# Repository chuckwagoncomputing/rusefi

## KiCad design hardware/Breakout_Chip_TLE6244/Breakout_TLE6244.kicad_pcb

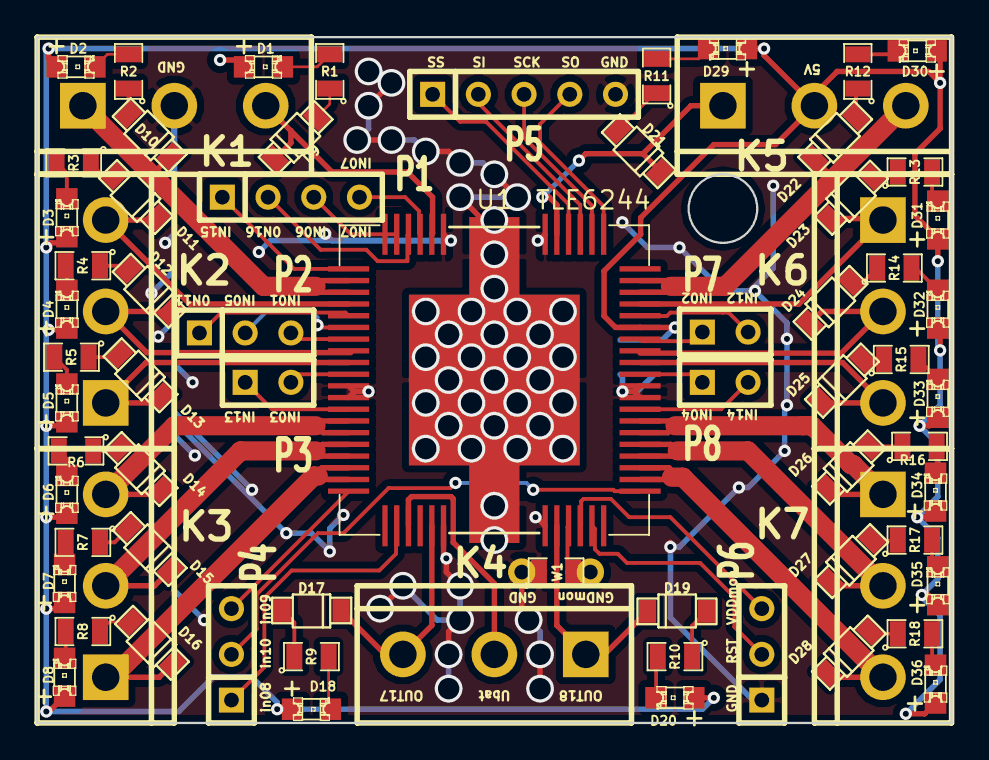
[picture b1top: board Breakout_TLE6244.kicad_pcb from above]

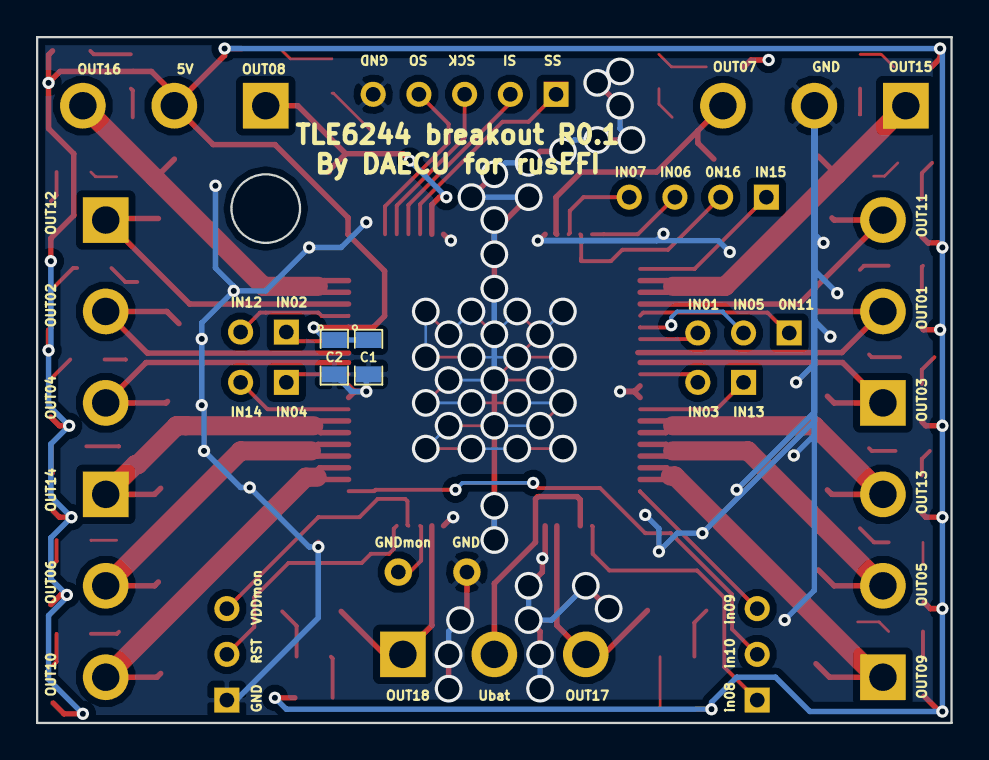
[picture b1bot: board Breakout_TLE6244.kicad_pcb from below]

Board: 4 copper layers, 50.8 x 38.1 mm, 73 parts (2 on the bottom side), 80 nets.

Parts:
C1: 1uF; SM0805
C2: .01uF; SM0805
D1, D2, D3, D4, D5, D6, D7, D8, D18, D20, D29, D30, D31, D32, D33, D34, D35, D36: LED-red; LED-0805_A
D9, D10, D11, D12, D13, D14, D15, D16, D17, D19, D21, D22, D23, D24, D25, D26, D27, D28: DIODE; SOD-123
K1, K2, K3, K4, K5, K6, K7: CONN_3; bornier3
P1: CONN_4; SIL-4
P2, P4, P6: CONN_3; SIL-3
P3, P7, P8: CONN_2; SIL-2
P5: CONN_5; SIL-5
R1, R2, R3, R4, R5, R6, R7, R8, R9, R10, R11, R12, R13, R14, R15, R16, R17, R18: 1K; SM0805
U1: TLE6244; HiQUAD64
W1: TEST; SM0805_jumper

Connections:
/5v: C1.1, C2.1, D1.1, D2.1, D3.1, D4.1, D5.1, D6.1, D7.1, D8.1, D18.1, D20.1, D29.1, D30.1, D31.1, D32.1, D33.1, D34.1, D35.1, D36.1, K5.2, U1.47
/GNDmon: U1.29, W1.2
/RST: P6.2, U1.31
/SCK: P5.3, U1.54
/SI: P5.2, U1.55
/SO: P5.4, U1.53
/SS: P5.1, U1.56
/Ubatt: K4.2, U1.23
/VDDmon: P6.3, U1.30
/in01: P2.3, U1.7
/in02: P7.1, U1.46
/in03: P3.2, U1.10
/in04: P8.1, U1.43
/in05: P2.2, U1.6
/in06: P1.3, U1.63, U1.64
/in07: P1.4, U1.61
/in08: P4.1, U1.22
/in09: P4.3, U1.20
/in10: P4.2, U1.33
/in11: P2.1, U1.5
/in12: P7.2, U1.48
/in13: P3.1, U1.13
/in14: P8.2, U1.40
/in15: P1.1, U1.1
/in16: P1.2, U1.62
/out01: D12.2, K2.2, U1.8
/out02: D24.2, K6.2, U1.45
/out03: D13.2, K2.1, U1.9
/out04: D25.2, K6.3, U1.44
/out05: D15.2, K3.2, U1.16, U1.17
/out06: D27.2, K7.2, U1.36, U1.37
/out07: D9.2, K1.3, U1.60
/out08: D21.2, K5.1, U1.57
/out09: D16.2, K3.1, U1.18, U1.19
/out10: D28.2, K7.3, U1.34, U1.35
/out11: D11.2, K2.3, U1.4
/out12: D23.2, K6.1, U1.49
/out13: D14.2, K3.3, U1.14, U1.15
/out14: D26.2, K7.1, U1.38, U1.39
/out15: D10.2, K1.1, U1.2, U1.3
/out16: D22.2, K5.3, U1.50, U1.51
/out17: D17.2, K4.3, U1.25
/out18: D19.2, K4.1, U1.28
GND: C1.2, C2.2, K1.2, P5.5, P6.1, U1.11, U1.12, U1.26, U1.27, U1.41, U1.42, U1.58, U1.59, U1.slug, W1.1
unnamed: D9.1, R1.1
unnamed: D21.1, R11.1
unnamed: D29.2, R11.2
unnamed: D1.2, R1.2
unnamed: D17.1, R9.1
unnamed: D18.2, R9.2
unnamed: D3.2, R3.2
unnamed: D11.1, R3.1
unnamed: D22.1, R12.1
unnamed: D30.2, R12.2
unnamed: D2.2, R2.2
unnamed: D10.1, R2.1
unnamed: D27.1, R17.1
unnamed: D28.1, R18.1
unnamed: D36.2, R18.2
unnamed: D35.2, R17.2
unnamed: D26.1, R16.1
unnamed: D34.2, R16.2
unnamed: D25.1, R15.1
unnamed: D33.2, R15.2
unnamed: D19.1, R10.1
unnamed: D20.2, R10.2
unnamed: D5.2, R5.2
unnamed: D7.2, R7.2
unnamed: D15.1, R7.1
unnamed: D14.1, R6.1
unnamed: D6.2, R6.2
unnamed: D13.1, R5.1
unnamed: D12.1, R4.1
unnamed: D4.2, R4.2
unnamed: D24.1, R14.1
unnamed: D32.2, R14.2
unnamed: D23.1, R13.1
unnamed: D31.2, R13.2
unnamed: D16.1, R8.1
unnamed: D8.2, R8.2

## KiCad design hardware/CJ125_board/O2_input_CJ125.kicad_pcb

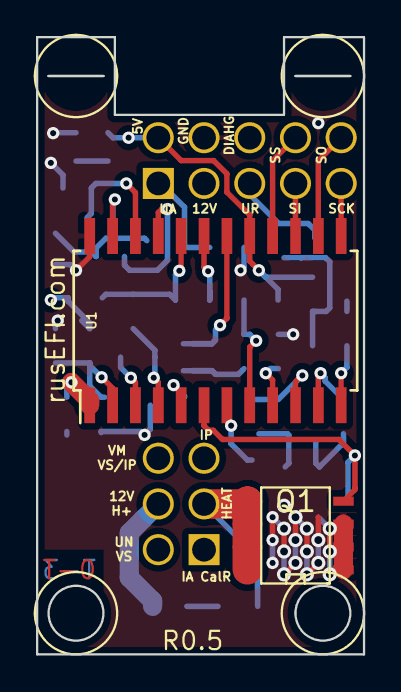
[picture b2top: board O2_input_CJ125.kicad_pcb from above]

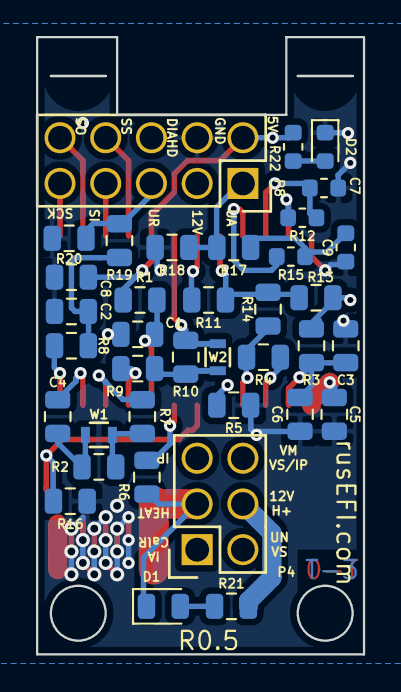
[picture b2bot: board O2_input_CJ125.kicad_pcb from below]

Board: 4 copper layers, 18.2 x 34.3 mm, 39 parts (37 on the bottom side), 35 nets.

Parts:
C1: 1000pF; C_0805_2012Metric
C2, C6, C8: 0.033uF; C_0805_2012Metric
C3: DNP; C_0805_2012Metric
C4: 0.1uF; C_0805_2012Metric
C5: 220pf; C_0805_2012Metric
C7: 0.1uF; C_0603_1608Metric
C9: 0.033uF; C_0603_1608Metric
D1: LED-RED; LED_0805_2012Metric
D2: LED-GRN; LED_0603_1608Metric
P4: CONN_02X03; Socket_Strip_Straight_2x03
P8: CONN_02X05; Socket_Strip_Straight_2x05
Q1: FDS2734; SO8E_ST
R1, R5, R7, R16, R18, R20: 10k; R_0805_2012Metric
R2: 21k6; R_0805_2012Metric
R3: 0R; R_0805_2012Metric
R4: 61.9; R_0805_2012Metric
R6, R17, R19: 6.8k; R_0805_2012Metric
R8: 1k; R_0805_2012Metric
R9: 82.5; R_0805_2012Metric
R10: 220; R_0805_2012Metric
R11: 5.11k; R_0805_2012Metric
R12: 100k; R_0603_1608Metric
R13: 100k; R_0805_2012Metric
R14: 511k; R_0805_2012Metric
R15, R22: 1k; R_0603_1608Metric
R21: 4.7k; R_0805_2012Metric
U1: CJ125; SOIC-24_7.5x15.4mm_Pitch1.27mm
W1, W2: TEST; R_0603

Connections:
/CF: C7.2, R12.1, U1.22
/CJ125_5v: C8.2, P8.2, R1.2, R22.1, U1.17
/CJ125_HEATER: D1.1, P4.3, Q1.2, R6.2
/CJ125_IA: P4.1, R4.2, R14.1, U1.4
/CJ125_IP: P4.5, R4.1, U1.3
/CJ125_SCK: P8.9, U1.13
/CJ125_SI: P8.7, U1.15
/CJ125_SO: P8.10, U1.14
/CJ125_SS: P8.8, U1.16
/CJ125_UA: C9.2, R15.1, R17.2
/CJ125_UN: P4.2, R3.2, R13.1
/CJ125_UR: C2.1, R8.2, R19.2
/CJ125_VM: P4.6, R10.1, U1.18, W2.2
/CM: C4.2, U1.11
/DIAHD: R6.1, U1.7
/DIAHG: P8.6, Q1.1, R16.2, U1.6
/OSZ: R5.2, U1.5
/RF: R12.2, U1.23
/RM: R7.1, U1.10
/RS: R9.2, U1.9
/RST: C1.1, R1.1, U1.8
/UA: R15.2, U1.21
/UN: C3.1, C5.1, R3.1, U1.2
/UP: R11.1, R13.2, R14.2, U1.20
/UR: R8.1, U1.12
/US: R11.2, U1.19
/WO2-12V: C6.2, P4.4, P8.3, R21.2, U1.1
GND: C1.2, C2.2, C3.2, C5.2, C6.1, C7.1, C8.1, C9.1, D2.1, P8.4, Q1.3, R5.1, R16.1, R18.2, R20.2, U1.24
unnamed: C4.1, R2.2, W1.1
unnamed: D1.2, R21.1
unnamed: D2.2, R22.2
unnamed: P8.1, R17.1, R18.1
unnamed: P8.5, R19.1, R20.1
unnamed: R2.1, R7.2, W1.2
unnamed: R9.1, R10.2, W2.1

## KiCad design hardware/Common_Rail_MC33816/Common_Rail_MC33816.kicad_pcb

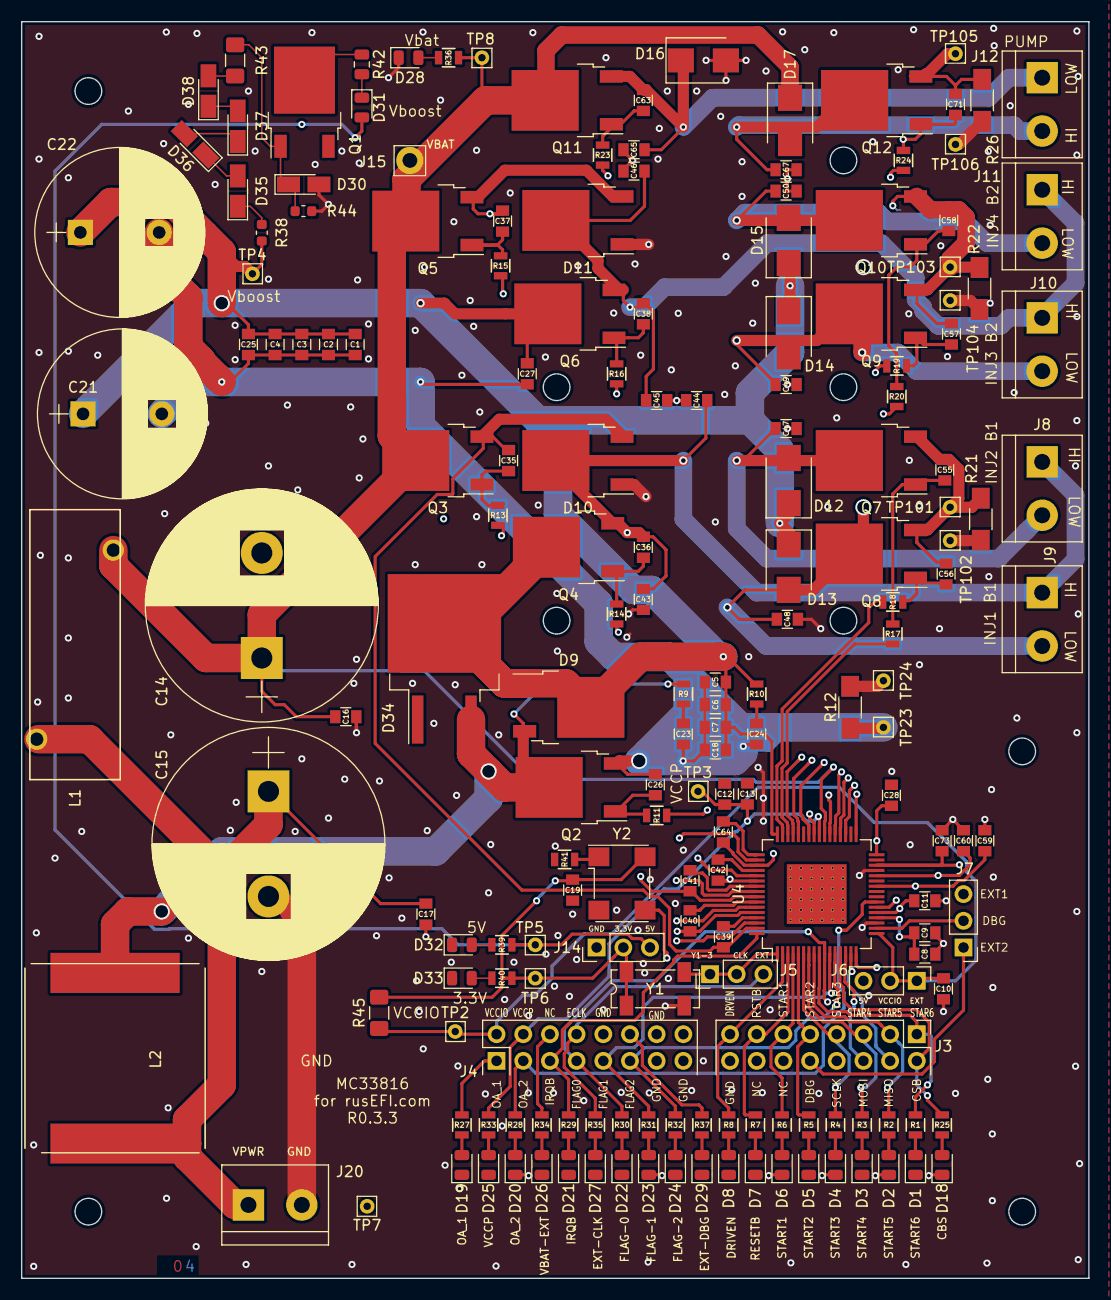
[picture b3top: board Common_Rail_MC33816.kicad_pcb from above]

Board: 4 copper layers, 101.6 x 119.6 mm, 183 parts (0 on the bottom side), 108 nets.

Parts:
C1, C3, C5, C7: 100nF; C_0805
C2, C4, C6, C18: 10nF; C_0805
C8, C10, C11, C13: 0.1uF; C_0805
C9: 1uF; C_0805
C12: 4.7uF; C_0805
C14, C15: 1000uF; CP_Radial_D22.0mm_P10.00mm_SnapIn
C16, C17: 220nF; C_0805
C19, C35, C36, C37, C38, C55, C56, C57, C58, C63, C71: 1000pF; C_0805
C21, C22: 390uF; CP_Radial_D16.0mm_P7.50mm
C23, C24, C28, C59, C60, C73: 330pF; C_0805
C25, C27: 0.22uF; C_0805
C26: 470pF; C_0805
C39, C40, C41, C42, C64: 0.33uF; C_0805
C43, C44, C45, C46, C47, C48, C49, C50, C65, C67: 4700pF; C_0805
D1, D2, D3, D4, D5, D6, D7, D8, D18, D19, D20, D21, D22, D23, D24, D25, D26, D27, D28, D29, D31, D32, D33: LED_Small; LED_0805_2012Metric
D9: FFD10UP20S; TO-252-2
D10, D11: SBR10200CTL; TO-252-2
D12, D13, D14, D15, D16, D17: STPS2H100UY; D_SMB
D30, D35, D36, D37, D38: 5.7V; D_MicroMELF_Handsoldering
D34: STTH802G-TR; TO-263-2
J3, J4: CONN_02X08; Pin_Header_Straight_2x08_Pitch2.54mm
J5, J6, J7, J14: CONN_01X03; Pin_Header_Straight_1x03_Pitch2.54mm
J8, J9, J10, J11, J12: INJ_Term; TerminalBlock_bornier-2_P5.08mm
J15: CONN_01X01; Pin_D1.4mm_L8.5mm_W2.8mm_FlatFork
J20: Conn_01x02; TerminalBlock_bornier-2_P5.08mm
L1: 6uH; 744710610-Inductor
L2: 10uH; IHLP6767GZER100M01
Q1, Q2, Q3, Q4, Q5, Q6, Q7, Q8, Q9, Q10, Q11, Q12: BUK9230-100B; TO-252-2
R1, R2, R3, R4, R5, R6, R7, R8, R25, R27, R28, R29, R30, R31, R32, R33, R34, R35, R36, R37, R39, R40: 1k; R_0805
R9, R10: 5.1R; R_0805
R11, R13, R14, R15, R16, R17, R18, R19, R20, R23, R24, R41: 10R; R_0805
R12, R21, R22, R26: 0R010; R_1206_HandSoldering
R38, R44: 10k; R_0603_1608Metric
R42: 1k; R_0805_2012Metric
R43, R45: 0R010; R_1206_3216Metric_Pad1.42x1.75mm_HandSolder
TP2, TP3, TP4, TP5, TP6, TP7, TP8, TP23, TP24, TP101, TP102, TP103, TP104, TP105, TP106: CONN_01X01; Pin_D0.7mm_L6.5mm_W1.8mm_FlatFork
U4: MC33816; HTQFP-64-1EP_10x10mm_Pitch0.5mm_ThermalPad_for_MC33816
Y1: 1MHz; Crystal_SMD_SeikoEpson_MC306-4pin_8.0x3.2mm
Y2: 1MHz; Oscillator_SMD_Diodes_FN-4Pin_7.0x5.0mm

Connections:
/3.3V: C19.1, J14.2, R40.2, R45.1, TP6.1, Y1.1, Y1.4, Y2.4
/5V: C11.1, D31.2, J6.3, J14.3, R39.2, TP5.1, U4.21
/BANK1_BAT: C35.2, C39.2, D10.3, Q3.3, U4.63
/BANK2_BAT: C37.2, C41.2, D11.3, Q5.3, U4.57
/CLK: J5.1, J5.2, U4.1, Y1.3, Y2.3
/CSB: J3.2, R25.2, U4.13
/DBG: J7.2, U4.18
/DBG_EXT1: J4.12, J7.3, R37.2
/DBG_EXT2: J3.10, J7.1
/DRVEN: J3.15, R8.2, U4.2
/EXT_CLK: J4.8, J5.3, R35.2
/FLAG_0: J4.7, R30.2, U4.10
/FLAG_1: J4.9, R31.2, U4.11
/FLAG_2: J4.11, R32.2, U4.12
/G_HB1_BAT: R13.2, U4.62
/G_HB1_BST: R14.2, U4.59
/G_HB2_BAT: R15.2, U4.56
/G_HB2_BST: R16.2, U4.53
/G_LS6: R23.2, U4.50
/G_L_BOOST: R11.2, U4.41
/G_L_INJ1: R18.2, U4.47
/G_L_INJ2: R17.2, U4.46
/G_L_INJ3: R19.2, U4.45
/G_L_INJ4: R20.2, U4.44
/G_PUMP: R24.2, U4.42
/INJ1_LOW: C48.1, D13.2, J9.2, Q8.2, U4.38
/INJ2_LOW: C47.1, D12.2, J8.2, Q7.2, U4.37
/INJ3_LOW: C49.1, D14.2, J10.2, Q9.2, U4.36
/INJ4_LOW: C50.1, D15.2, J11.2, Q10.2, U4.35
/INJ_B1_HIGH: C36.2, C40.2, C43.1, C44.1, D10.2, J8.1, J9.1, Q4.3, U4.60
/INJ_B2_HIGH: C38.2, C42.2, C45.1, C46.1, D11.2, J10.1, J11.1, Q6.3, U4.54
/IRQB: J4.5, R29.2, U4.64
/MISO: J3.4, U4.15
/MOSI: J3.6, U4.14
/OA_1: J4.1, R27.2, U4.22
/OA_2: J4.3, R28.2, U4.23
/PUMP_HIGH: C63.2, C64.1, C65.1, D16.1, J12.1, Q11.3, U4.51
/PUMP_LOW: C67.1, D17.2, J12.2, Q12.2, U4.33
/P_B1_SENSE: C55.1, C56.1, C59.1, Q7.3, Q8.3, R21.1, TP101.1, U4.26
/P_B2_SENSE: C57.1, C58.1, C60.1, Q9.3, Q10.3, R22.1, TP103.1, U4.28
/P_SENSE_BOOST: C1.2, C2.2, C3.2, C4.2, C5.2, C6.2, C7.2, C18.2, C21.2, C22.2, C23.2, C24.2, C25.2, C26.1, C27.2, C28.1, Q2.3, R12.1, TP23.1, U4.32
/P_SENSE_PUMP: C71.1, C73.1, Q12.3, R26.1, TP105.1, U4.30
/RESETB: J3.13, R7.2, U4.3
/SCLK: J3.8, U4.16
/START1: J3.11, R6.2, U4.4
/START2: J3.9, R5.2, U4.5
/START3: J3.7, R4.2, U4.6
/START4: J3.5, R3.2, U4.7
/START5: J3.3, R2.2, U4.8
/START6: J3.1, R1.2, U4.9
/VBAT_EXT: J4.6, R34.2
/VCC2P5: C8.1, C9.1, U4.20
/VCCIO: C10.1, J4.2, J6.1, J6.2, R45.2, TP2.1, U4.17
/VCCP: C12.1, C13.1, J4.4, R33.2, TP3.1, U4.40
/Vbat: C14.1, C16.1, D17.1, J15.1, L1.2, Q3.2, Q5.2, Q11.2, R36.2, TP8.1, U4.39
/Vboost: C1.1, C2.1, C3.1, C4.1, C5.1, C6.1, C7.1, C18.1, C21.1, C22.1, C25.1, C27.1, D9.1, D9.2, D12.1, D13.1, D14.1, D15.1, D34.2, Q4.2, Q6.2, R10.1, R38.2, TP4.1, U4.48
/Vbuck: D9.3, D34.3, L2.1, Q2.2, R9.1
/Vpwr: C15.1, C17.1, J20.1, L1.1, L2.2
GND: C8.2, C9.2, C10.2, C11.2, C12.2, C13.2, C14.2, C15.2, C16.2, C17.2, C19.2, C28.2, C43.2, C44.2, C45.2, C46.2, C47.2, C48.2, C49.2, C50.2, C59.2, C60.2, C65.2, C67.2, C73.2, D1.1, D2.1, D3.1, D4.1, D5.1, D6.1, D7.1, D8.1, D10.1, D11.1, D16.2, D18.1, D19.1, D20.1, D21.1, D22.1, D23.1, D24.1, D25.1, D26.1, D27.1, D28.1, D29.1, D30.2, D32.1, D33.1, J3.16, J4.10, J4.13, J4.15, J4.16, J14.1, J20.2, Q1.3, R12.2, R21.2, R22.2, R26.2, R41.1, R44.1, TP7.1, TP24.1, TP102.1, TP104.1, TP106.1, U4.19, U4.24, U4.25, U4.27, U4.29, U4.31, U4.65, Y1.2, Y2.2
unnamed: C23.1, R9.2
unnamed: C24.1, R10.2
unnamed: C26.2, Q2.1, R11.1
unnamed: C35.1, Q3.1, R13.1
unnamed: C36.1, Q4.1, R14.1
unnamed: C37.1, Q5.1, R15.1
unnamed: C38.1, Q6.1, R16.1
unnamed: C39.1, U4.61
unnamed: C40.1, U4.58
unnamed: C41.1, U4.55
unnamed: C42.1, U4.52
unnamed: C55.2, Q7.1, R17.1
unnamed: C56.2, Q8.1, R18.1
unnamed: C57.2, Q9.1, R19.1
unnamed: C58.2, Q10.1, R20.1
unnamed: C63.1, Q11.1, R23.1
unnamed: C64.2, U4.49
unnamed: C71.2, Q12.1, R24.1
unnamed: D1.2, R1.1
unnamed: D2.2, R2.1
unnamed: D3.2, R3.1
unnamed: D4.2, R4.1
unnamed: D5.2, R5.1
unnamed: D6.2, R6.1
unnamed: D7.2, R7.1
unnamed: D8.2, R8.1
unnamed: D18.2, R25.1
unnamed: D19.2, R27.1
unnamed: D20.2, R28.1
unnamed: D21.2, R29.1
unnamed: D22.2, R30.1
unnamed: D23.2, R31.1
unnamed: D24.2, R32.1
unnamed: D25.2, R33.1
unnamed: D26.2, R34.1
unnamed: D27.2, R35.1
unnamed: D28.2, R36.1
unnamed: D29.2, R37.1
unnamed: D30.1, Q1.1, R43.2, R44.2
unnamed: D31.1, R42.2
unnamed: D32.2, R39.1
unnamed: D33.2, R40.1
unnamed: D35.1, R38.1
unnamed: D35.2, D36.1
unnamed: D36.2, D37.1
unnamed: D37.2, D38.1
unnamed: D38.2, R43.1
unnamed: Q1.2, R42.1
unnamed: R41.2, Y2.1

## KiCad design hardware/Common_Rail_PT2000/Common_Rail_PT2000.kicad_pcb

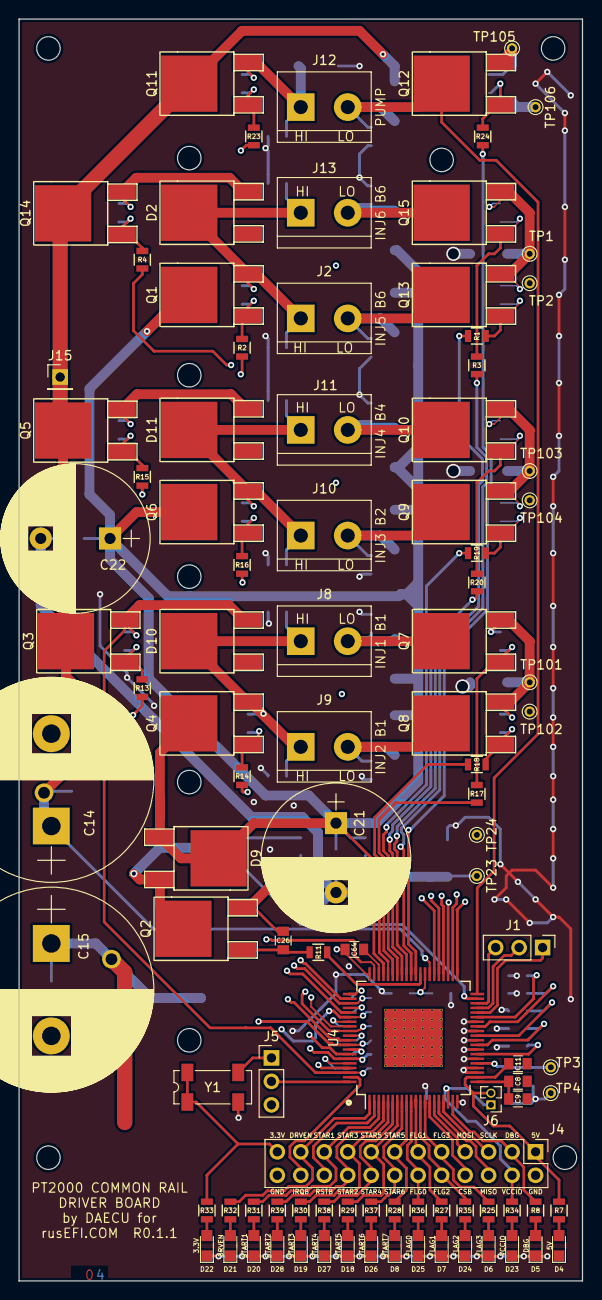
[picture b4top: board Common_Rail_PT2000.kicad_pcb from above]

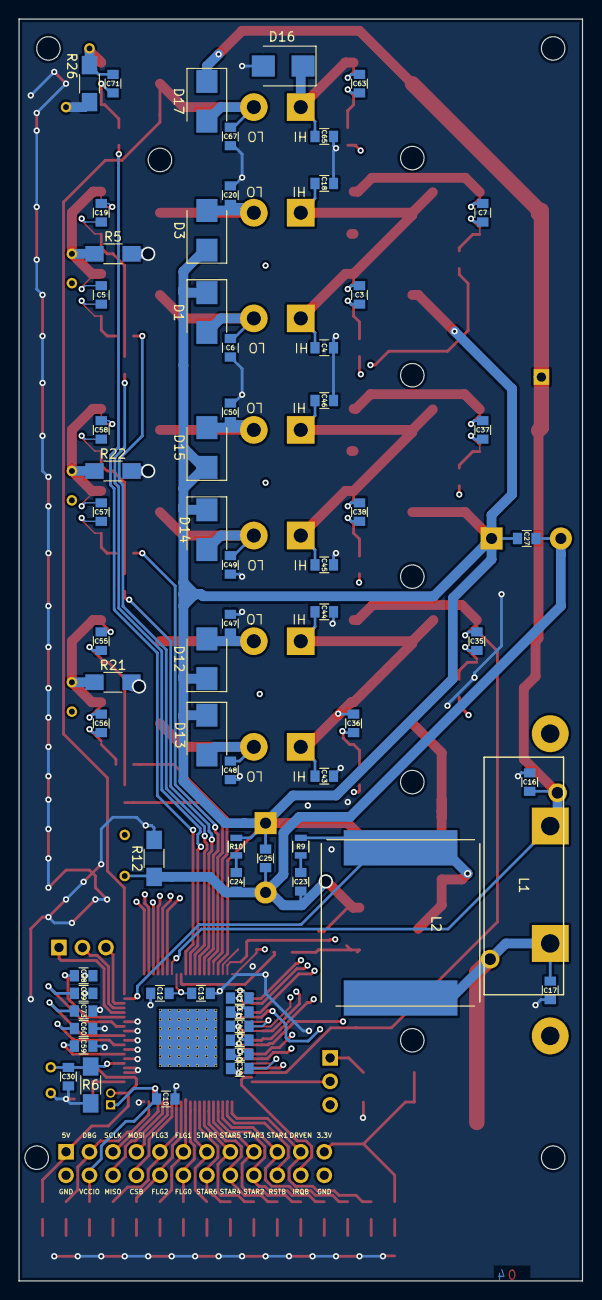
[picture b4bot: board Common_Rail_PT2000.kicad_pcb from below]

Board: 4 copper layers, 61.0 x 136.5 mm, 168 parts (67 on the bottom side), 109 nets.

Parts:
C1, C2, C39, C40, C41, C42, C64: 0.33uF; C_0805
C3, C5, C7, C19, C35, C36, C37, C38, C55, C56, C57, C58, C63, C71: 1000pF; C_0805
C4, C6, C18, C20, C43, C44, C45, C46, C47, C48, C49, C50, C65, C67: 4700pF; C_0805
C8, C10, C11, C13: 0.1uF; C_0805
C9: 1uF; C_0805
C12: 4.7uF; C_0805
C14, C15: 1000uF; CP_Radial_D22.0mm_P10.00mm_SnapIn
C16, C17, C25, C27: 0.22uF; C_0805
C21, C22: 390uF; CP_Radial_D16.0mm_P7.50mm
C23, C24, C28, C29, C30, C59, C60, C73: 330pF; C_0805
C26: 470pF; C_0805
D1, D3, D12, D13, D14, D15, D16, D17: STPS2H100UY; D_SMB
D2, D10, D11: SBR10200CTL; TO-252-2Lead
D4, D5, D6, D7, D8, D18, D19, D20, D21, D22, D23, D24, D25, D26, D27, D28: LED_Small; LED_0805
D9: FFD10UP20S; TO-252-2Lead
J1, J5: CONN_01X03; Pin_Header_Straight_1x03_Pitch2.54mm
J2, J8, J9, J10, J11, J12, J13: INJ_Term; TerminalBlock_bornier-2_P5.08mm
J4: CONN_02X08; Pin_Header_Straight_2x12_Pitch2.54mm
J6: CONN_01X03; Pin_Header_Straight_1x02_Pitch1.27mm
J15: Conn_01x01; Pin_Header_Straight_1x01_Pitch2.54mm
L1: 6uH; 744710610-Inductor
L2: 10uH; IHLP6767GZER100M01
Q1, Q2, Q3, Q4, Q5, Q6, Q7, Q8, Q9, Q10, Q11, Q12, Q13, Q14, Q15: BUK9230-100B; TO-252-2Lead
R1, R2, R3, R4, R11, R13, R14, R15, R16, R17, R18, R19, R20, R23, R24: 10R; R_0805
R5, R6, R21, R22, R26: 0R015; R_1206_HandSoldering
R7, R8, R25, R27, R28, R29, R30, R31, R32, R33, R34, R35, R36, R37, R38, R39: 1k; R_0805
R9, R10: 5.1R; R_0805
R12: 0R010; R_1206_HandSoldering
TP1, TP2, TP3, TP4, TP23, TP24, TP101, TP102, TP103, TP104, TP105, TP106: Conn_01x01; PINTST
U4: PT2000; LQFP-80_12x12mm_Pitch0.5mmThermal
Y1: 1MHz; Crystal_SMD_SeikoEpson_MC306-4pin_8.0x3.2mm

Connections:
/3.3V: J4.23, R33.2, Y1.1, Y1.4
/5V: C11.1, J4.1, J6.2, R7.2, U4.22
/BANK1_BAT: C35.2, C39.2, D10.3, Q3.3, U4.78
/BANK2_BAT: C37.2, C41.2, D11.3, Q5.3, U4.72
/BANK3_BAT: C1.2, C7.2, D2.3, Q14.3, U4.66
/CLK: J5.2, U4.80
/CSB: J4.8, U4.14
/DBG: J4.3, R8.2, U4.19
/DRVEN: J4.21, R32.2, U4.1
/FLAG_0: J4.12, R36.2, U4.10
/FLAG_1: J4.11, R27.2, U4.11
/FLAG_2: J4.10, R35.2, U4.12
/FLAG_3: J4.9, R25.2, U4.13
/G_HB1_BAT: R13.2, U4.77
/G_HB1_BST: R14.2, U4.74
/G_HB2_BAT: R15.2, U4.71
/G_HB2_BST: R16.2, U4.68
/G_HB3_BAT: R4.2, U4.65
/G_HB3_BST: R2.2, U4.62
/G_LS7: R23.2, U4.59
/G_L_BOOST: R11.2, U4.49
/G_L_INJ1: R18.2, U4.56
/G_L_INJ2: R17.2, U4.55
/G_L_INJ3: R19.2, U4.54
/G_L_INJ4: R20.2, U4.53
/G_L_INJ5: R1.2, U4.52
/G_L_INJ6: R3.2, U4.51
/G_PUMP: R24.2, U4.50
/INJ1_LOW: C48.1, D13.2, J9.2, Q8.2, U4.46
/INJ2_LOW: C47.1, D12.2, J8.2, Q7.2, U4.45
/INJ3_LOW: C49.1, D14.2, J10.2, Q9.2, U4.44
/INJ4_LOW: C50.1, D15.2, J11.2, Q10.2, U4.43
/INJ5_LOW: C6.1, D1.2, J2.2, Q13.2, U4.42
/INJ6_LOW: C20.1, D3.2, J13.2, Q15.2, U4.41
/INJ_B1_HIGH: C36.2, C40.2, C43.1, C44.1, D10.2, J8.1, J9.1, Q4.3, U4.75
/INJ_B2_HIGH: C38.2, C42.2, C45.1, C46.1, D11.2, J10.1, J11.1, Q6.3, U4.69
/INJ_B3_HIGH: C2.2, C3.2, C4.1, C18.1, D2.2, J2.1, J13.1, Q1.3, U4.63
/IRQB: J4.22, U4.79
/MISO: J4.6, U4.16
/MOSI: J4.7, U4.15
/OA_1: J1.1, U4.36
/OA_2: J1.2, U4.37
/OA_3: J1.3, U4.38
/PUMP_HIGH: C63.2, C64.1, C65.1, D16.1, J12.1, Q11.3, U4.60
/PUMP_LOW: C67.1, D17.2, J12.2, Q12.2, U4.40
/P_B1_SENSE: C55.1, C56.1, C59.1, Q7.3, Q8.3, R21.1, TP101.1, U4.27
/P_B2_SENSE: C57.1, C58.1, C60.1, Q9.3, Q10.3, R22.1, TP103.1, U4.29
/P_B3_SENSE: C5.1, C19.1, C29.1, Q13.3, Q15.3, R5.1, TP1.1, U4.33
/P_SENSE_4: C30.1, R6.1, TP3.1, U4.25
/P_SENSE_BOOST: C21.2, C22.2, C23.2, C24.2, C25.2, C26.1, C27.2, C28.1, Q2.3, R12.1, TP23.1, U4.35
/P_SENSE_PUMP: C71.1, C73.1, Q12.3, R26.1, TP105.1, U4.31
/RESETB: J4.20, U4.2
/SCLK: J4.5, U4.17
/START1: J4.19, R31.2, U4.3
/START2: J4.18, R39.2, U4.4
/START3: J4.17, R30.2, U4.5
/START4: J4.16, R38.2, U4.6
/START5: J4.15, R29.2, U4.7
/START6: J4.14, R37.2, U4.8
/START7: J4.13, R28.2, U4.9
/VCC2P5: C8.1, C9.1, U4.21
/VCCIO: C10.1, J4.4, J6.1, R34.2, U4.18
/VCCP: C12.1, C13.1, U4.48
/Vbat: C14.1, C16.1, D17.1, J15.1, L1.2, Q3.2, Q5.2, Q11.2, Q14.2, U4.47
/Vboost: C21.1, C22.1, C25.1, C27.1, D1.1, D3.1, D9.1, D9.2, D12.1, D13.1, D14.1, D15.1, Q1.2, Q4.2, Q6.2, R10.1, U4.57
/Vbuck: D9.3, L2.1, Q2.2, R9.1, U4.39
/Vpwr: C15.1, C17.1, L1.1, L2.2
GND: C4.2, C6.2, C8.2, C9.2, C10.2, C11.2, C12.2, C13.2, C14.2, C15.2, C16.2, C17.2, C18.2, C20.2, C28.2, C29.2, C30.2, C43.2, C44.2, C45.2, C46.2, C47.2, C48.2, C49.2, C50.2, C59.2, C60.2, C65.2, C67.2, C73.2, D2.1, D4.1, D5.1, D6.1, D7.1, D8.1, D10.1, D11.1, D16.2, D18.1, D19.1, D20.1, D21.1, D22.1, D23.1, D24.1, D25.1, D26.1, D27.1, D28.1, J4.2, J4.24, R5.2, R6.2, R12.2, R21.2, R22.2, R26.2, TP2.1, TP4.1, TP24.1, TP102.1, TP104.1, TP106.1, U4.20, U4.23, U4.24, U4.26, U4.28, U4.30, U4.32, U4.34, U4.81, Y1.2
unnamed: C1.1, U4.64
unnamed: C2.1, U4.61
unnamed: C3.1, Q1.1, R2.1
unnamed: C5.2, Q13.1, R1.1
unnamed: C7.1, Q14.1, R4.1
unnamed: C19.2, Q15.1, R3.1
unnamed: C23.1, R9.2
unnamed: C24.1, R10.2
unnamed: C26.2, Q2.1, R11.1
unnamed: C35.1, Q3.1, R13.1
unnamed: C36.1, Q4.1, R14.1
unnamed: C37.1, Q5.1, R15.1
unnamed: C38.1, Q6.1, R16.1
unnamed: C39.1, U4.76
unnamed: C40.1, U4.73
unnamed: C41.1, U4.70
unnamed: C42.1, U4.67
unnamed: C55.2, Q7.1, R17.1
unnamed: C56.2, Q8.1, R18.1
unnamed: C57.2, Q9.1, R19.1
unnamed: C58.2, Q10.1, R20.1
unnamed: C63.1, Q11.1, R23.1
unnamed: C64.2, U4.58
unnamed: C71.2, Q12.1, R24.1
unnamed: D4.2, R7.1
unnamed: D5.2, R8.1
unnamed: D6.2, R25.1
unnamed: D7.2, R27.1
unnamed: D8.2, R28.1
unnamed: D18.2, R29.1
unnamed: D19.2, R30.1
unnamed: D20.2, R31.1
unnamed: D21.2, R32.1
unnamed: D22.2, R33.1
unnamed: D23.2, R34.1
unnamed: D24.2, R35.1
unnamed: D25.2, R36.1
unnamed: D26.2, R37.1
unnamed: D27.2, R38.1
unnamed: D28.2, R39.1
unnamed: J5.1, Y1.3

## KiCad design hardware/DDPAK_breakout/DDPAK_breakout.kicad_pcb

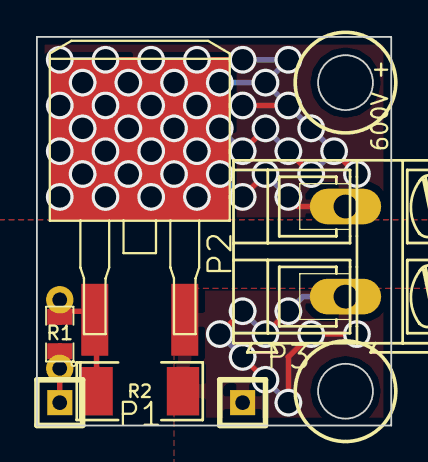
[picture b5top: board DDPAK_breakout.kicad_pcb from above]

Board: 2 copper layers, 19.7 x 21.6 mm, 6 parts (0 on the bottom side), 4 nets.

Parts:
P1, P3: CONN_1; SIL-1
P2: CONN_2; AK300-2
Q1: IRGS14C40L; m-pad-2.1-TO-263AB
R1: 1K; SM0805_jumper
R2: 100K; SM2010

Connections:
/GND: P2.2, P3.1, Q1.3, R2.2
/HV: P2.1, Q1.2
/SIG: P1.1, R1.1
/SIG2: Q1.1, R1.2, R2.1

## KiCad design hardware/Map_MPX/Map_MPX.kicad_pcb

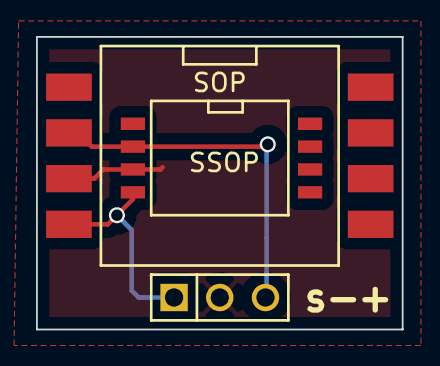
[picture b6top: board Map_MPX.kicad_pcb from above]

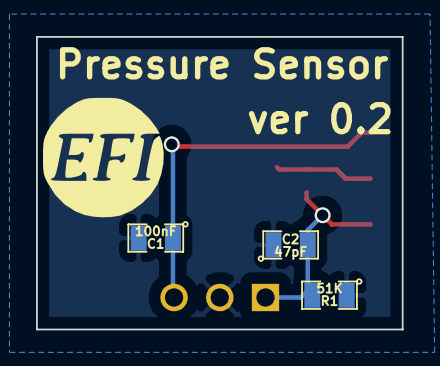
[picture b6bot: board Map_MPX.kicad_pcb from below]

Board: 2 copper layers, 20.3 x 16.3 mm, 4 parts (3 on the bottom side), 2 nets.

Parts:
C1: 100nF; SM0805
C2: 47pF; SM0805
R1: 51K; SM0805
SSOP: SOP; SSOP

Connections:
GND: C1.2, C2.1, R1.1
unnamed: C2.2, R1.2
